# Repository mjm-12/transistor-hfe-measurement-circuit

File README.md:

# Transistor hFE Measurement Circuit

Constant-current based circuit for measuring transistor hFE (KiCad project).

- v1.0: as ordered on 2026-07-02 (tag `v1.0`)
- v1.1: current revision (tag `v1.1`)

## Schematic

PDF: export from `transistor-hfe-measurement-circuit.kicad_sch` in KiCad 10.

## License

Copyright 2026 Hayata Yamamoto.

This hardware design is licensed under the CERN Open Hardware Licence Version 2 - Permissive (CERN-OHL-P-2.0). See [LICENSE](LICENSE).

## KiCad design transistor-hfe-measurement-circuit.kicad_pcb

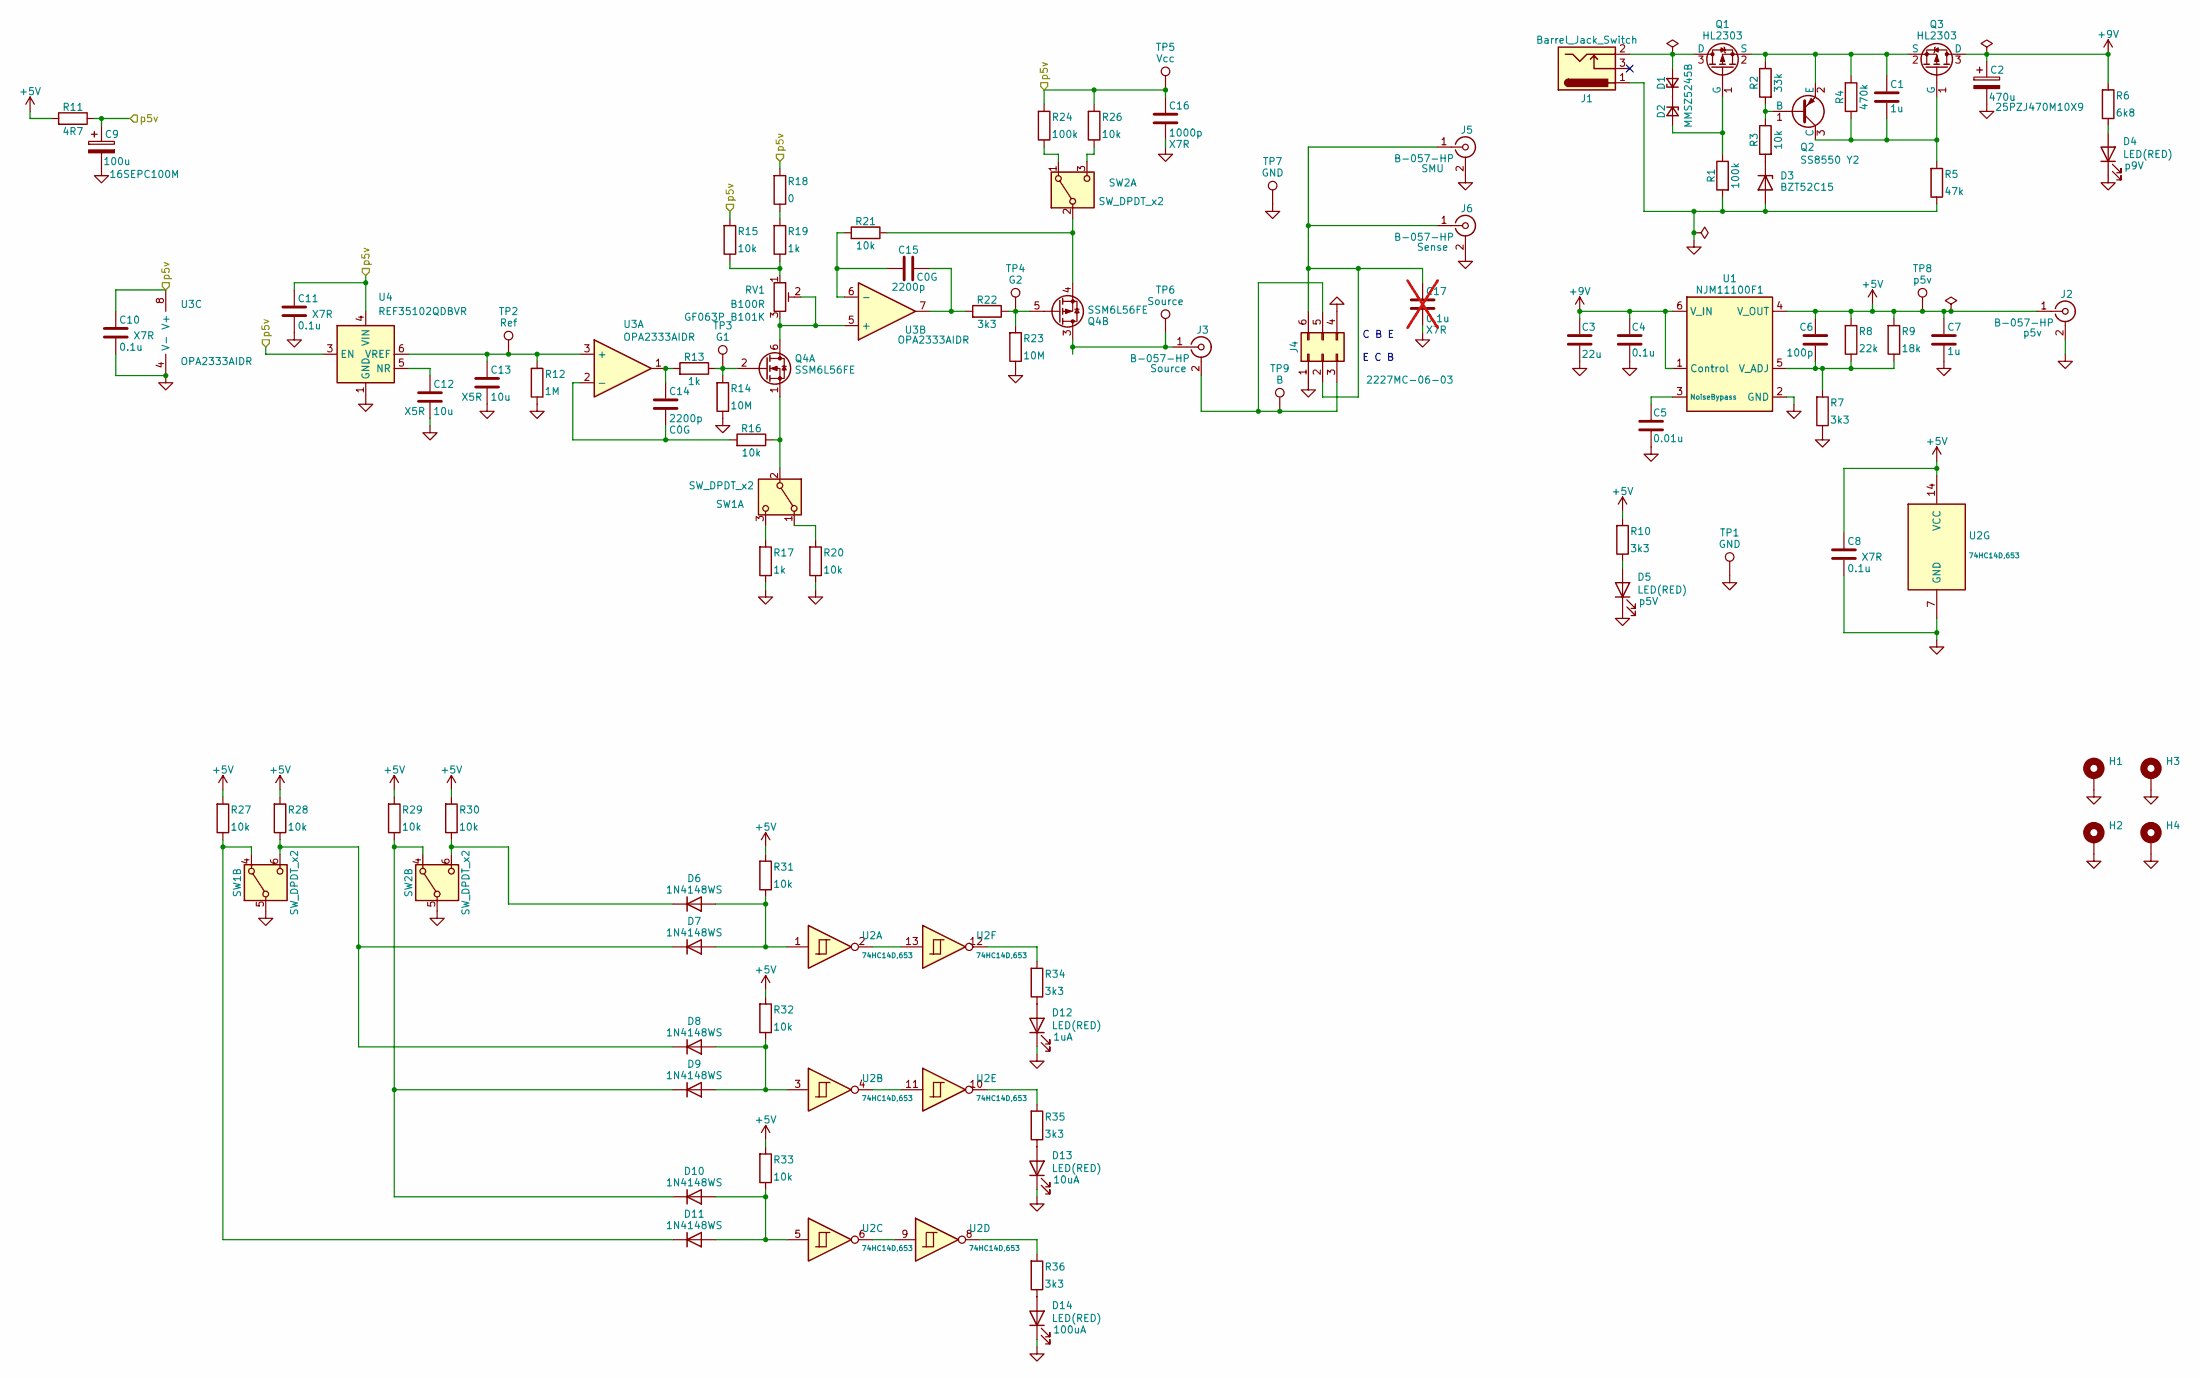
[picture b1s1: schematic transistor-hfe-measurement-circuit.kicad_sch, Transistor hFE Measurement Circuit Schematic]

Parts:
C1, C7: 1u; C_0805_2012Metric; LCSC C28323
C2: 470u; CP_Radial_D10.0mm_P5.00mm; MPN 25PZJ470M10X9
C3: 22u; C_1206_3216Metric; LCSC C12891
C4, C8, C10, C11: 0.1u; C_0603_1608Metric; LCSC C14663
C5: 0.01u; C_0603_1608Metric; LCSC C57112
C6: 100p; C_0603_1608Metric; LCSC C14858
C9: 100u; CP_Radial_D6.3mm_P2.50mm; MPN 16SEPC100M
C12, C13: 10u; C_0603_1608Metric; LCSC C96446
C14, C15: 2200p; C_0805_2012Metric; LCSC C28260
C16: 1000p; C_0603_1608Metric; LCSC C1588
C17: 0.1u; C_1206_3216Metric; LCSC C24497; not fitted
D1, D2: MMSZ5245B; D_SOD-123; LCSC C19077428
D3: BZT52C15; D_SOD-123; LCSC C19077412
D4, D5, D12, D13, D14: LED(RED); D_0603_1608Metric_Name; LCSC C2286
D6, D7, D8, D9, D10, D11: 1N4148WS; D_SOD-323; LCSC C2128
H1, H2, H3, H4: MountingHole_Pad; MountingHole_3.2mm_M3_DIN965_Pad
J1: Barrel_Jack_Switch; MJ-179PH_Edge
J2, J3, J5, J6: B-057-HP; COSMTEC_B-057-HP
J4: 2227MC-06-03; DIP-6_W7.62mm_Socket
Q1, Q3: HL2303; SOT-23; LCSC C7420345
Q2: SS8550 Y2; SOT-23; LCSC C8542
Q4: SSM6L56FE; SOT-563; LCSC C17604697
R1, R24: 100k; R_0603_1608Metric; LCSC C25803
R2: 33k; R_0603_1608Metric; LCSC C4216
R3, R15, R16, R20, R21, R26, R27, R28, R29, R30, R31, R32, R33: 10k; R_0603_1608Metric; LCSC C25804
R4: 470k; R_0603_1608Metric; LCSC C23178
R5: 47k; R_0603_1608Metric; LCSC C25819
R6: 6k8; R_0603_1608Metric; LCSC C23212
R7, R10, R22, R34, R35, R36: 3k3; R_0603_1608Metric; LCSC C22978
R8: 22k; R_0603_1608Metric; LCSC C31850
R9: 18k; R_0603_1608Metric; LCSC C25810
R11: 4R7; R_0805_2012Metric; LCSC C17675
R12: 1M; R_0603_1608Metric; LCSC C22935
R13, R17, R19: 1k; R_0603_1608Metric; LCSC C21190
R14, R23: 10M; R_0603_1608Metric; LCSC C7250
R18: 0; R_0603_1608Metric; LCSC C21189
RV1: B100R; TCOS_GF063P; MPN GF063P B101K
SW1, SW2: SW_DPDT_x2; SW_NKK_SS22SDP2
TP1, TP2, TP3, TP4, TP5, TP6, TP7, TP8, TP9: TestPoint; TestPoint_THTPad_D2.0mm_Drill1.0mm_ValueSilk-name
U1: NJM11100F1; SOT-23-6_Handsoldering
U2: 74HC14D,653; SOIC-14_3.9x8.7mm_P1.27mm; LCSC C5605
U3: OPA2333AIDR; SOIC-8_3.9x4.9mm_P1.27mm
U4: REF35102QDBVR; SOT-23-6

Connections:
+5V: C6.1, C7.1, C8.1, J2.1 (In), R8.1, R9.1, R10.1, R11.1, R27.1, R28.1, R29.1, R30.1, R31.1, R32.1, R33.1, TP8.1 (1_1), U1.4 (V_OUT), U2.14 (VCC)
+9V: C2.1, C3.1, C4.1, Q3.3 (D), R6.1, U1.1 (Control), U1.6 (V_IN)
/p5v: C9.1, C10.1, C11.1, C16.1, R11.2, R15.1, R18.1, R24.1, R26.1, TP5.1 (1_1), U3.8 (V+), U4.3 (EN), U4.4 (VIN)
GNDPWR: C2.2, C3.2, C4.2, C5.2, C7.2, C8.2, C9.2, C10.2, C11.2, C12.2, C13.2, C16.2, C17.2, D3.2 (A), D4.1 (K), D5.1 (K), D12.1 (K), D13.1 (K), D14.1 (K), H1.1 (1_1), H2.1 (1_1), H3.1 (1_1), H4.1 (1_1), J1.1, J2.2 (Ext), J4.1, J4.4, J5.2 (Ext), J6.2 (Ext), R1.1, R5.2, R7.2, R12.2, R14.2, R17.2, R20.2, R23.2, SW1.5 (B), SW2.5 (B), TP1.1 (1_1), TP7.1 (1_1), U1.2 (GND), U2.7 (GND), U3.4 (V-), U4.1 (GND), U4.2 (GND)
unnamed: C14.1, R13.1, U3.1
unnamed: C15.2, R22.1, U3.7
unnamed: D1.2 (A), J1.2, Q1.3 (D)
unnamed: D1.1 (K), D2.1 (K)
unnamed: D2.2 (A), Q1.1 (G), R1.2
unnamed: D3.1 (K), R3.1
unnamed: D4.2 (A), R6.2
unnamed: D5.2 (A), R10.2
unnamed: D6.2 (A), D7.2 (A), R31.2, U2.1
unnamed: D6.1 (K), R30.2, SW2.6 (C)
unnamed: D7.1 (K), D8.1 (K), R28.2, SW1.6 (C)
unnamed: D8.2 (A), D9.2 (A), R32.2, U2.3
unnamed: D10.2 (A), D11.2 (A), R33.2, U2.5
unnamed: D9.1 (K), D10.1 (K), R29.2, SW2.4 (A)
unnamed: D11.1 (K), R27.2, SW1.4 (A)
unnamed: D12.2 (A), R34.2
unnamed: D13.2 (A), R35.2
unnamed: D14.2 (A), R36.2
unnamed: J3.2 (Ext), J4.3, J4.5, TP9.1 (1_1)
unnamed: J3.1 (In), Q4.3 (D), TP6.1 (1_1)
unnamed: C17.1, J4.2, J4.6, J5.1 (In), J6.1 (In)
unnamed: C1.1, Q1.2 (S), Q2.2 (E), Q3.2 (S), R2.2, R4.1
unnamed: Q2.1 (B), R2.1, R3.2
unnamed: C1.2, Q2.3 (C), Q3.1 (G), R4.2, R5.1
unnamed: Q4.6 (D), RV1.2, RV1.3, U3.5 (+)
unnamed: Q4.2 (G), R13.2, R14.1, TP3.1 (1_1)
unnamed: Q4.1 (S), R16.2, SW1.2 (B)
unnamed: Q4.5 (G), R22.2, R23.1, TP4.1 (1_1)
unnamed: Q4.4 (S), R21.2, SW2.2 (B)
unnamed: R15.2, R19.2, RV1.1
unnamed: R18.2, R19.1
unnamed: R34.1, U2.12
unnamed: R35.1, U2.10
unnamed: R36.1, U2.8
unnamed: R20.1, SW1.1 (A)
unnamed: R17.1, SW1.3 (C)
unnamed: R24.2, SW2.1 (A)
unnamed: R26.2, SW2.3 (C)
unnamed: C5.1, U1.3 (NoiseBypass)
unnamed: C6.2, R7.1, R8.2, R9.2, U1.5 (V_ADJ)
unnamed: U2.6, U2.9
unnamed: U2.4, U2.11
unnamed: U2.2, U2.13
unnamed: C13.1, R12.1, TP2.1 (1_1), U3.3 (+), U4.6 (VREF)
unnamed: C14.2, R16.1, U3.2 (-)
unnamed: C15.1, R21.1, U3.6 (-)
unnamed: C12.1, U4.5 (NR)

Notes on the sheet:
C B E E C B

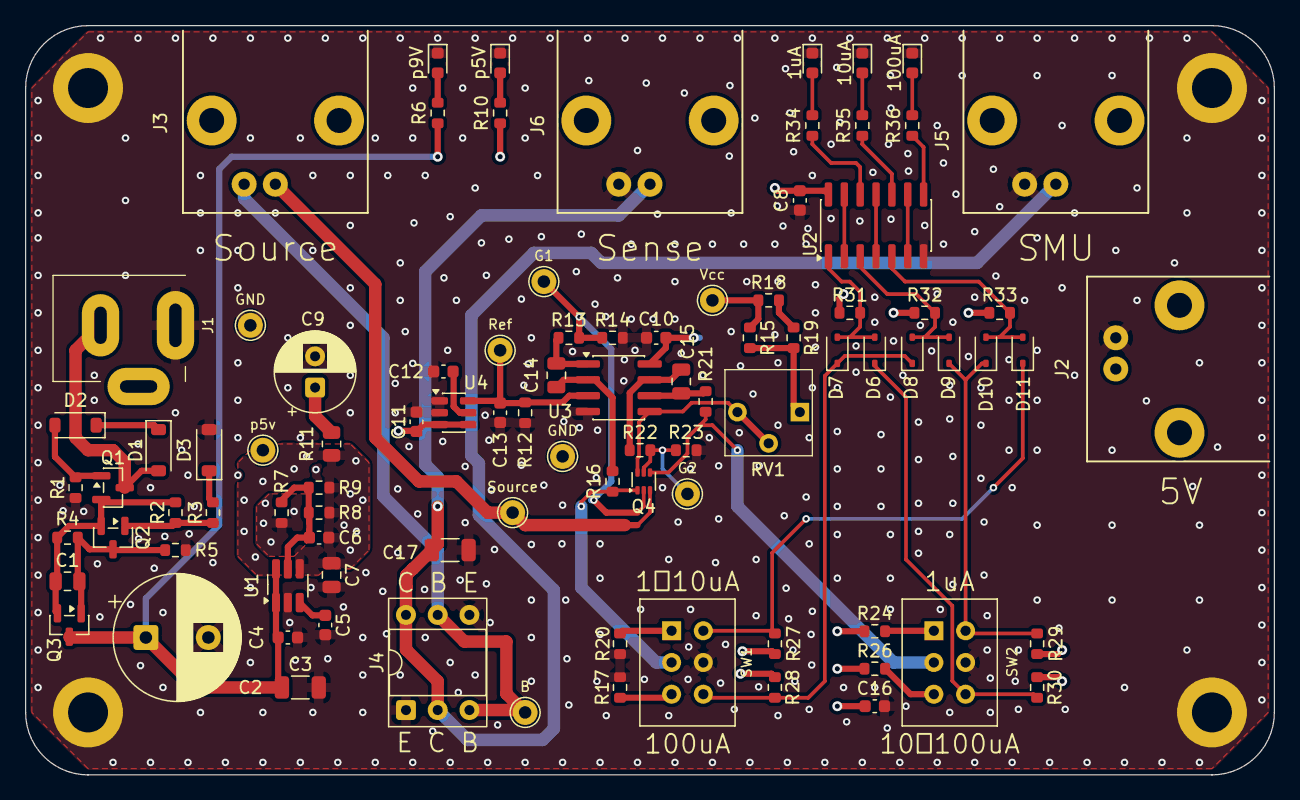
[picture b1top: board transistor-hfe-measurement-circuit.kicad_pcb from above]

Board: 4 copper layers, 100.0 x 60.0 mm, 96 parts (0 on the bottom side), 51 nets.

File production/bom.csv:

Designator,Footprint,Quantity,Value,LCSC Part #
"C1, C7",0805,2,1u,C28323
"C10, C11, C4, C8",0603,4,0.1u,C14663
"C12, C13",0603,2,10u,C96446
"C14, C15",0805,2,2200p,C28260
C16,0603,1,1000p,C1588
C3,1206,1,22u,C12891
C5,0603,1,0.01u,C57112
C6,0603,1,100p,C14858
"D1, D2",D_SOD-123,2,MMSZ5245B,C19077428
"D10, D11, D6, D7, D8, D9",D_SOD-323,6,1N4148WS,C2128
"D12, D13, D14, D4, D5",0603,5,LED(RED),C2286
D3,D_SOD-123,1,BZT52C15,C19077412
"Q1, Q3",SOT-23,2,HL2303,C7420345
Q2,SOT-23,1,SS8550 Y2,C8542
Q4,SOT-563,1,SSM6L56FE,C17604697
"R1, R24",0603,2,100k,C25803
"R10, R22, R34, R35, R36, R7",0603,6,3k3,C22978
R11,0805,1,4R7,C17675
R12,0603,1,1M,C22935
"R13, R17, R19",0603,3,1k,C21190
"R14, R23",0603,2,10M,C7250
"R15, R16, R20, R21, R26, R27, R28, R29, R3, R30, R31, R32, R33",0603,13,10k,C25804
"R18, R25",0603,2,0,C21189
R2,0603,1,33k,C4216
R4,0603,1,470k,C23178
R5,0603,1,47k,C25819
R6,0603,1,6k8,C23212
R8,0603,1,22k,C31850
R9,0603,1,18k,C25810
U2,SOIC-14_3.9x8.7mm_P1.27mm,1,"74HC14D,653",C5605

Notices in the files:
transistor-hfe-measurement-circuit.kicad_pcb:
Licensed under CERN-OHL-P v2
